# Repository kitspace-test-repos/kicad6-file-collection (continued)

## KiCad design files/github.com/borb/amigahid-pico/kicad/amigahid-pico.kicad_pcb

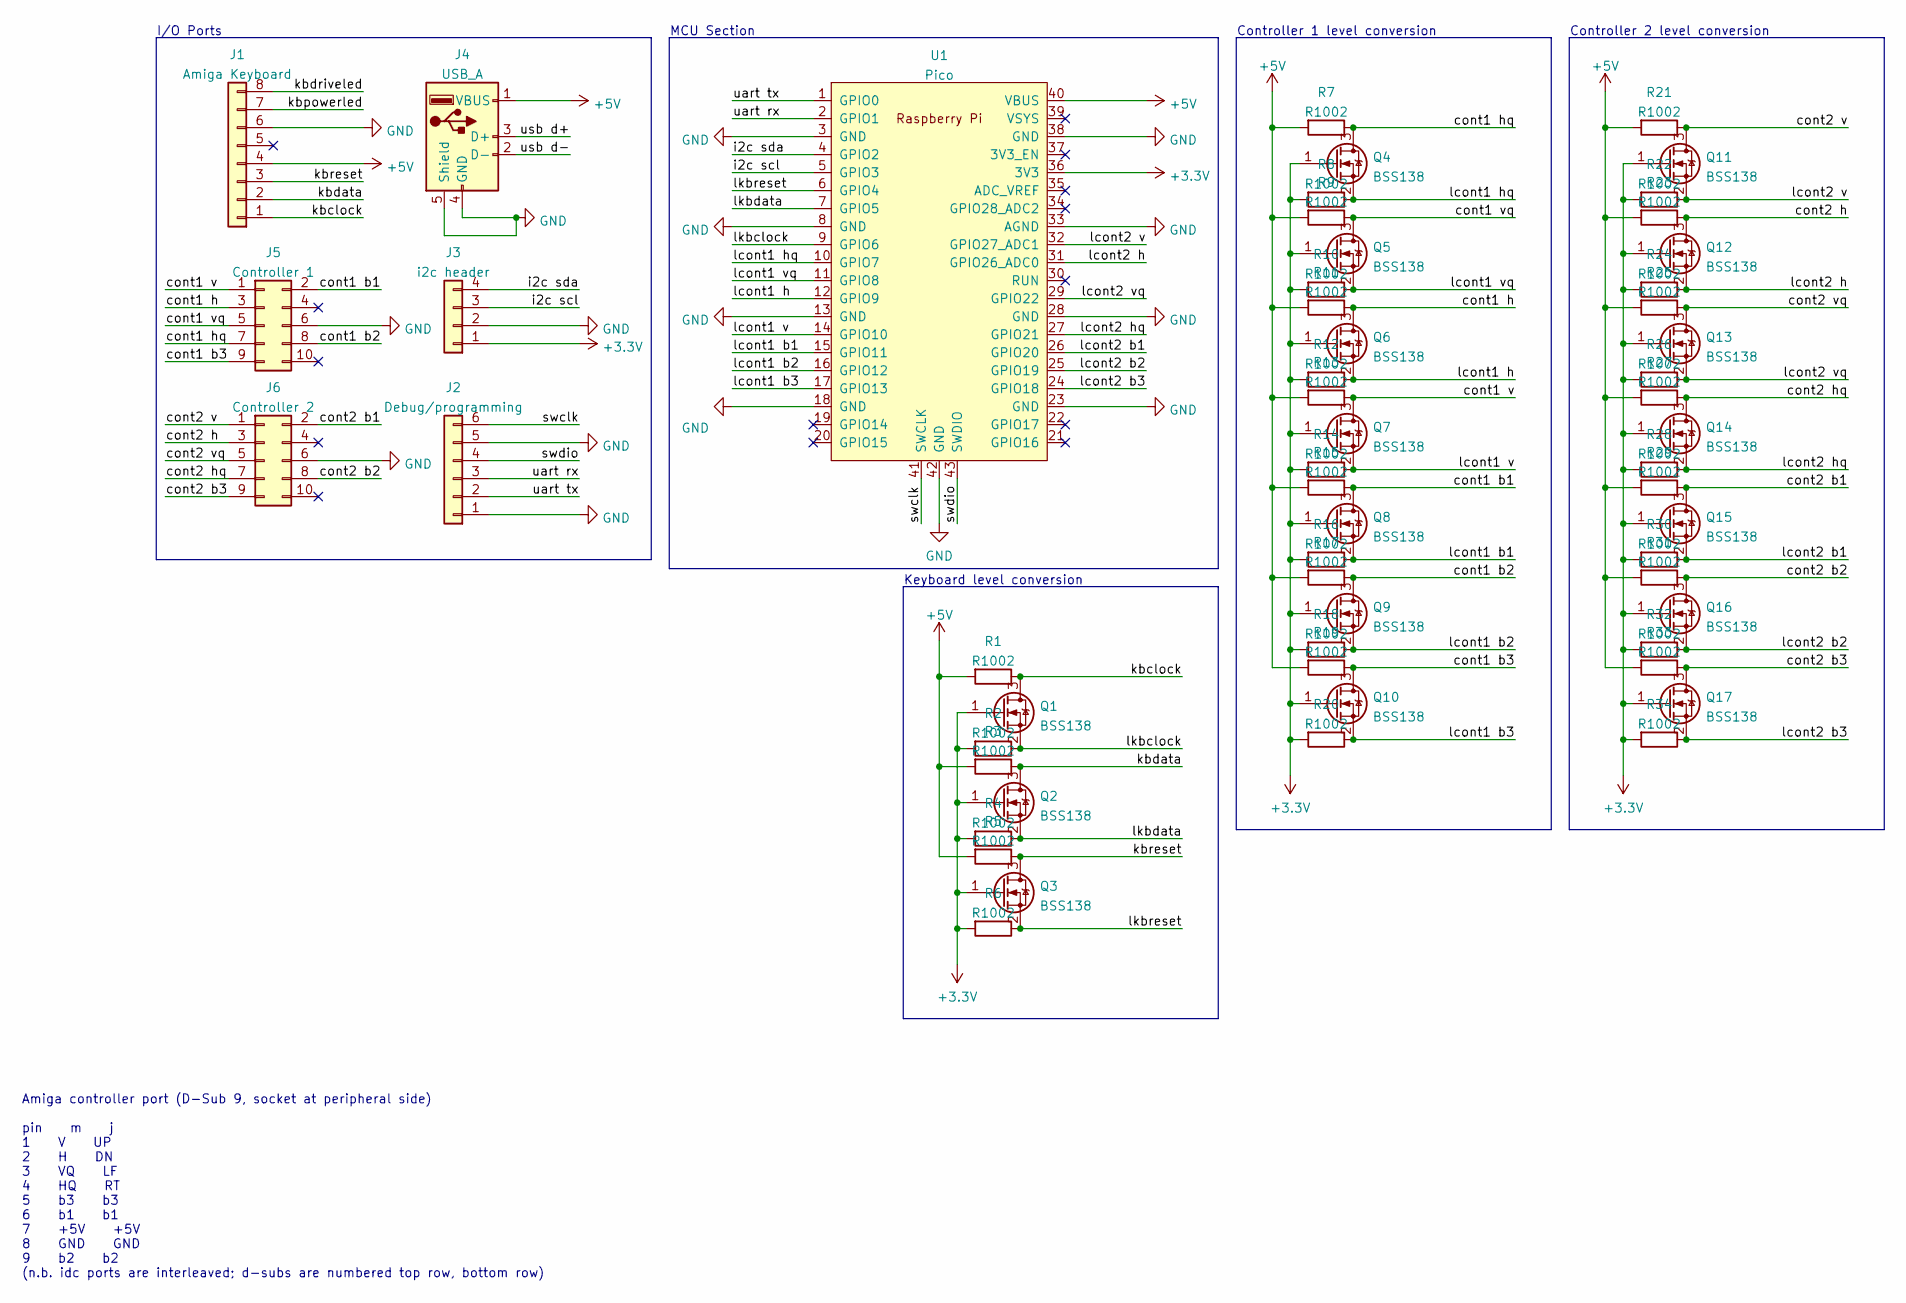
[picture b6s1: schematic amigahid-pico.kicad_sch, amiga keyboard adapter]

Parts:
J1: Amiga Keyboard; PinHeader_1x08_P2.54mm_Vertical
J2: Debug/programming; PinHeader_1x06_P2.54mm_Horizontal
J3: i2c header; PinHeader_1x04_P2.54mm_Vertical
J4: USB_A; USB_A_Molex_67643_Horizontal
J5: Controller 1; IDC-Header_2x05_P2.54mm_Vertical
J6: Controller 2; IDC-Header_2x05_P2.54mm_Vertical
Q1, Q2, Q3, Q4, Q5, Q6, Q7, Q8, Q9, Q10, Q11, Q12, Q13, Q14, Q15, Q16, Q17: BSS138; SOT-23
R1, R2, R3, R4, R5, R6, R7, R8, R9, R10, R11, R12, R13, R14, R15, R16, R17, R18, R19, R20, R21, R22, R23, R24, R25, R26, R27, R28, R29, R30, R31, R32, R33, R34: R1002; R_0603_1608Metric
U1: Pico; RPi_Pico_SMD_TH

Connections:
+3V3: J3.1, Q1.1 (G), Q2.1 (G), Q3.1 (G), Q4.1 (G), Q5.1 (G), Q6.1 (G), Q7.1 (G), Q8.1 (G), Q9.1 (G), Q10.1 (G), Q11.1 (G), Q12.1 (G), Q13.1 (G), Q14.1 (G), Q15.1 (G), Q16.1 (G), Q17.1 (G), R2.2, R4.2, R6.2, R8.2, R10.2, R12.2, R14.2, R16.2, R18.2, R20.2, R22.2, R24.2, R26.2, R28.2, R30.2, R32.2, R34.2, U1.36 (3V3)
+5V: J1.4, J4.1 (VBUS), R1.2, R3.2, R5.2, R7.2, R9.2, R11.2, R13.2, R15.2, R17.2, R19.2, R21.2, R23.2, R25.2, R27.2, R29.2, R31.2, R33.2, U1.40 (VBUS); also elsewhere on the board
/cont1 b1: J5.2, Q8.3 (D), R15.1; also elsewhere on the board
/cont1 b2: J5.8, Q9.3 (D), R17.1
/cont1 b3: J5.9, Q10.3 (D), R19.1
/cont1 h: J5.3, Q6.3 (D), R11.1
/cont1 hq: J5.7, Q4.3 (D), R7.1
/cont1 v: J5.1, Q7.3 (D), R13.1
/cont1 vq: J5.5, Q5.3 (D), R9.1
/cont2 b1: J6.2, Q15.3 (D), R29.1
/cont2 b2: J6.8, Q16.3 (D), R31.1
/cont2 b3: J6.9, Q17.3 (D), R33.1
/cont2 h: J6.3, Q12.3 (D), R23.1
/cont2 hq: J6.7, Q14.3 (D), R27.1
/cont2 v: J6.1, Q11.3 (D), R21.1
/cont2 vq: J6.5, Q13.3 (D), R25.1
/i2c scl: J3.3, U1.5 (GPIO3)
/i2c sda: J3.4, U1.4 (GPIO2)
/kbclock: J1.1, Q1.3 (D), R1.1
/kbdata: J1.2, Q2.3 (D), R3.1
/kbdriveled: J1.8
/kbpowerled: J1.7
/kbreset: J1.3, Q3.3 (D), R5.1
/lcont1 b1: Q8.2 (S), R16.1, U1.15 (GPIO11)
/lcont1 b2: Q9.2 (S), R18.1, U1.16 (GPIO12)
/lcont1 b3: Q10.2 (S), R20.1, U1.17 (GPIO13)
/lcont1 h: Q6.2 (S), R12.1, U1.12 (GPIO9)
/lcont1 hq: Q4.2 (S), R8.1, U1.10 (GPIO7)
/lcont1 v: Q7.2 (S), R14.1, U1.14 (GPIO10)
/lcont1 vq: Q5.2 (S), R10.1, U1.11 (GPIO8)
/lcont2 b1: Q15.2 (S), R30.1, U1.26 (GPIO20)
/lcont2 b2: Q16.2 (S), R32.1, U1.25 (GPIO19)
/lcont2 b3: Q17.2 (S), R34.1, U1.24 (GPIO18)
/lcont2 h: Q12.2 (S), R24.1, U1.31 (GPIO26_ADC0)
/lcont2 hq: Q14.2 (S), R28.1, U1.27 (GPIO21)
/lcont2 v: Q11.2 (S), R22.1, U1.32 (GPIO27_ADC1)
/lcont2 vq: Q13.2 (S), R26.1, U1.29 (GPIO22)
/lkbclock: Q1.2 (S), R2.1, U1.9 (GPIO6)
/lkbdata: Q2.2 (S), R4.1, U1.7 (GPIO5)
/lkbreset: Q3.2 (S), R6.1, U1.6 (GPIO4)
/swclk: J2.6, U1.41 (SWCLK)
/swdio: J2.4, U1.43 (SWDIO)
/uart rx: J2.3, U1.2 (GPIO1)
/uart tx: J2.2, U1.1 (GPIO0)
/usb d+: J4.3 (D+)
/usb d-: J4.2 (D-)
GND: J1.6, J2.1, J2.5, J3.2, J4.4 (GND), J4.5 (Shield), J5.6, J6.6, U1.3 (GND), U1.8 (GND), U1.13 (GND), U1.18 (GND), U1.23 (GND), U1.28 (GND), U1.33 (AGND), U1.38 (GND), U1.42 (GND)

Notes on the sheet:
Amiga controller port (D-Sub 9, socket at peripheral side) pin m j 1 V UP 2 H DN 3 VQ LF 4 HQ RT 5 b3 b3 6 b1 b1 7 +5V +5V 8 GND GND 9 b2 b2 (n.b. idc ports are interleaved; d-subs are numbered top row, bottom row)
MCU Section
I/O Ports
Controller 1 level conversion
Controller 2 level conversion
Keyboard level conversion

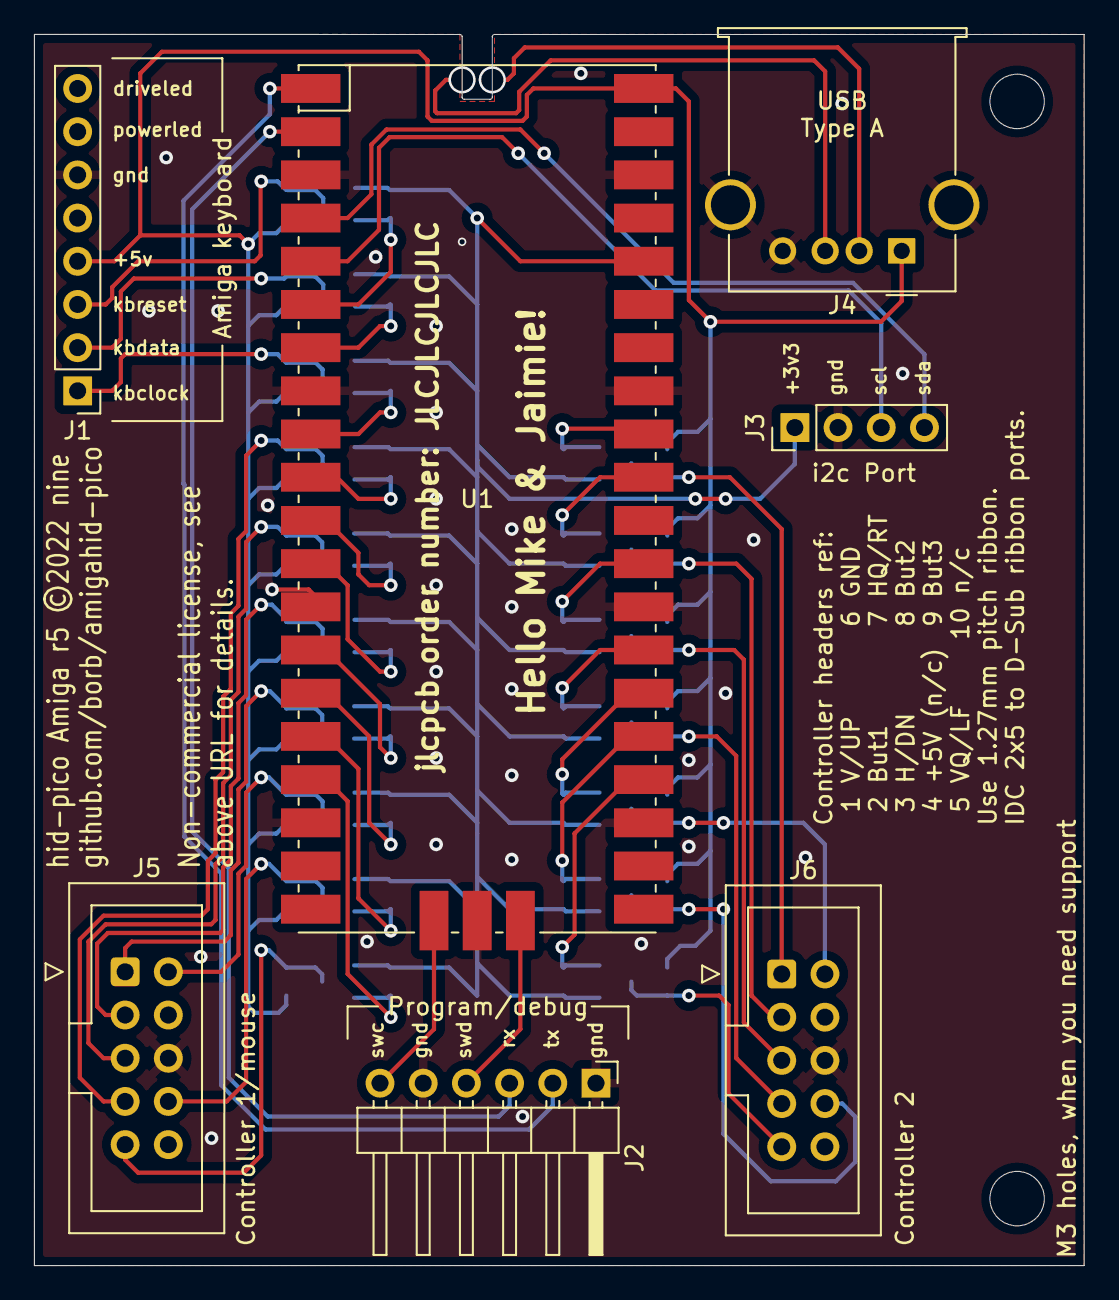
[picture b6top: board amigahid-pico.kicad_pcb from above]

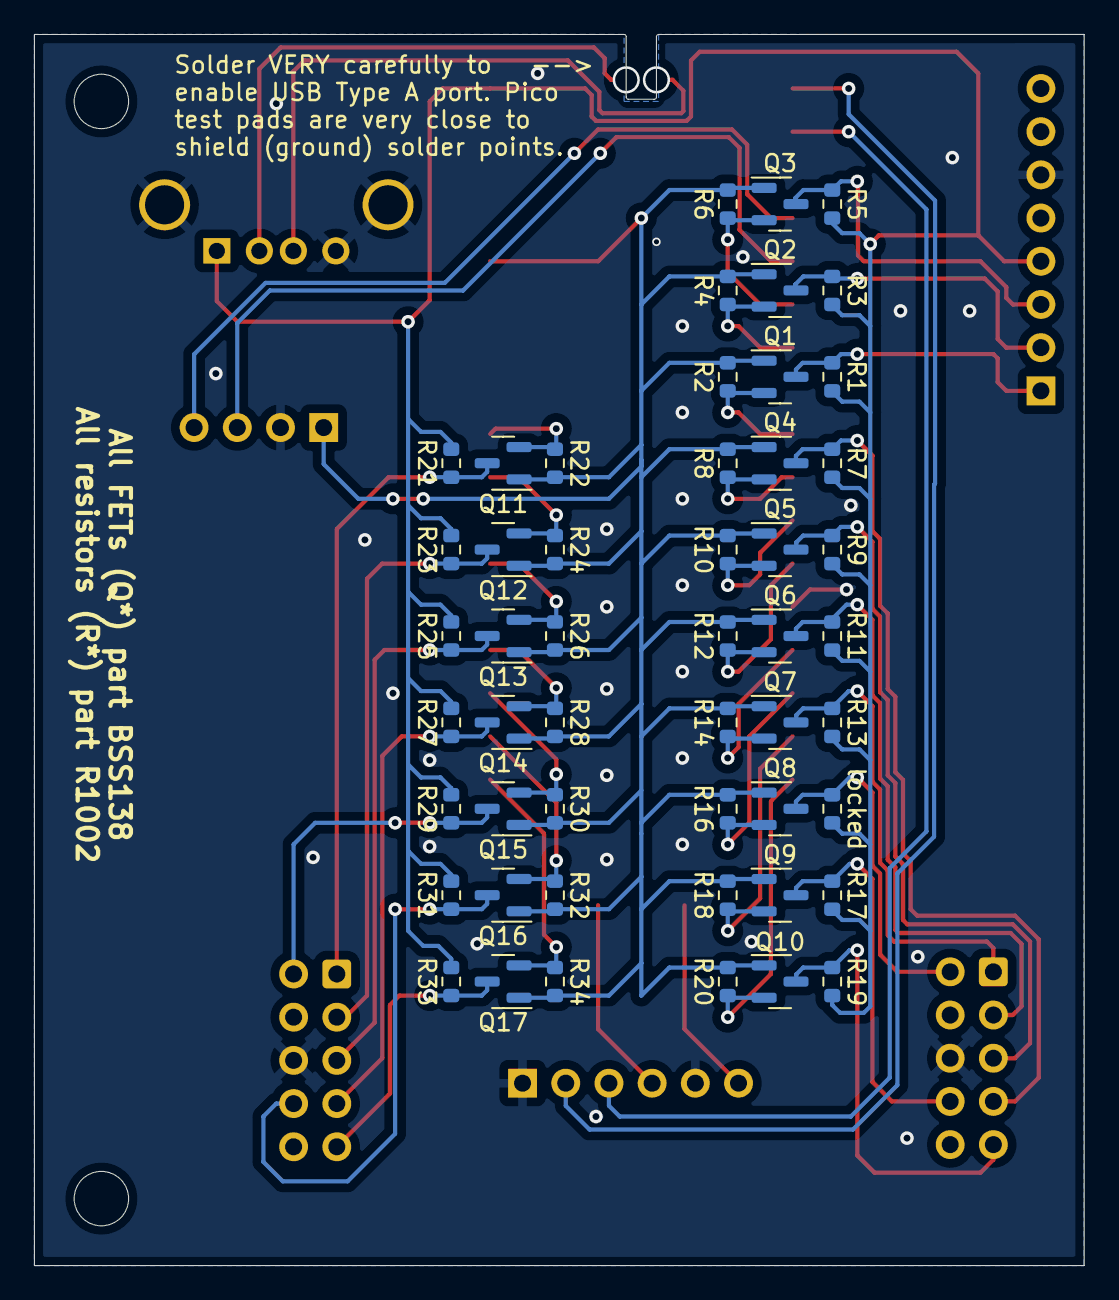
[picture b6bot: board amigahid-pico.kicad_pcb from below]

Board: 2 copper layers, 61.7 x 72.4 mm, 60 parts (51 on the bottom side), 43 nets.

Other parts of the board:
REF01, REF02: MountingHole_3.2mm_M3
locked: R1002; R_0603_1608Metric

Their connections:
+5V: locked.2; also elsewhere on the board
/cont1 b1: locked.1; also elsewhere on the board

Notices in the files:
files/github.com/borb/amigahid-pico/kicad/amigahid-pico.kicad_pcb:
hid-pico Amiga r5 ©️2022 nine
